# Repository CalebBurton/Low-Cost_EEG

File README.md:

# Low-Cost EEG
___Repo for storing files related to the Low-Cost EEG project at Stellenbosch University during the 2018 Global Health Technologies exchange with Northwestern University.___

---

Hardware is modified from the [OpenBCI Ganglion](https://github.com/OpenBCI/Ganglion_Hardware_Design_Files), firmware is copied directly from the [Ganglion library](https://github.com/OpenBCI/OpenBCI_Ganglion_Library) with no modification.

All design files were made with [KiCad](http://kicad-pcb.org/) EDA software.

Tested with Arduino IDE v1.8.5, utilizing Simblee library v1.1.4 from [https://www.simblee.com/package_simblee166_index.json](https://www.simblee.com/package_simblee166_index.json). See [this page](https://www.simblee.com/support.html) for instructions on adding an external board to your board manager.

Programmed using an [FTDI cable](https://www.adafruit.com/product/70). FTDI drivers are not yet supported on macOS versions 10.11.0 and above, so programming was done in a Windows 10 virtual machine.

The OpenBCI GUI, used for visualizing and analyzing the output data, can be downloaded from [OpenBCI's downloads page](http://openbci.com/index.php/downloads). OpenBCI also provides documentation for the [Ganglion](http://docs.openbci.com/Tutorials/02-Ganglion_Getting%20Started_Guide) and the [GUI](http://docs.openbci.com/OpenBCI%20Software/01-OpenBCI_GUI).

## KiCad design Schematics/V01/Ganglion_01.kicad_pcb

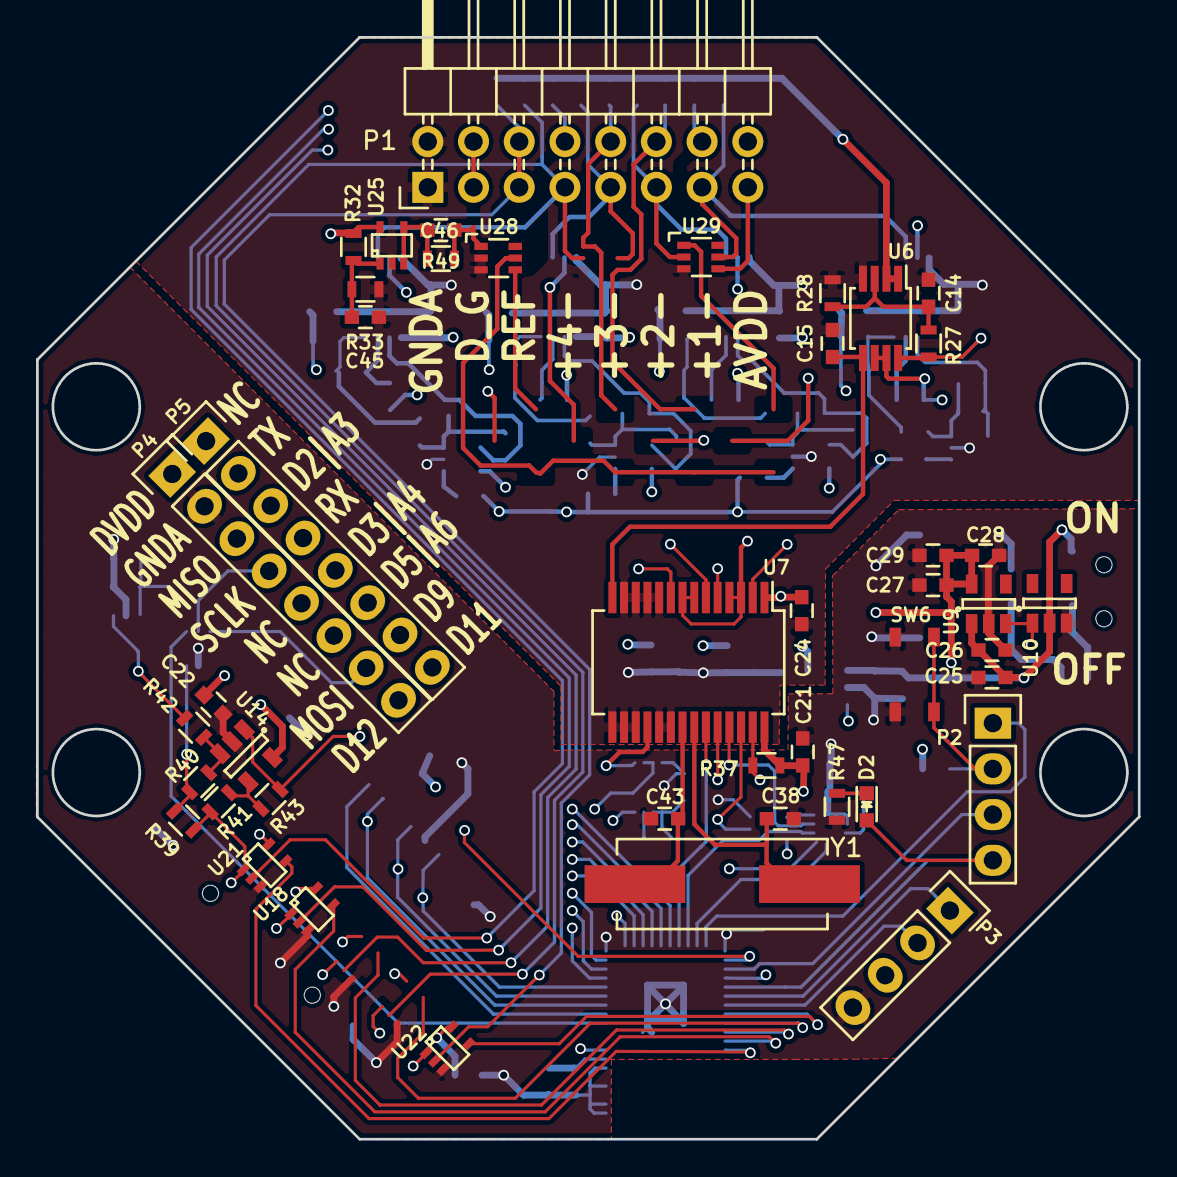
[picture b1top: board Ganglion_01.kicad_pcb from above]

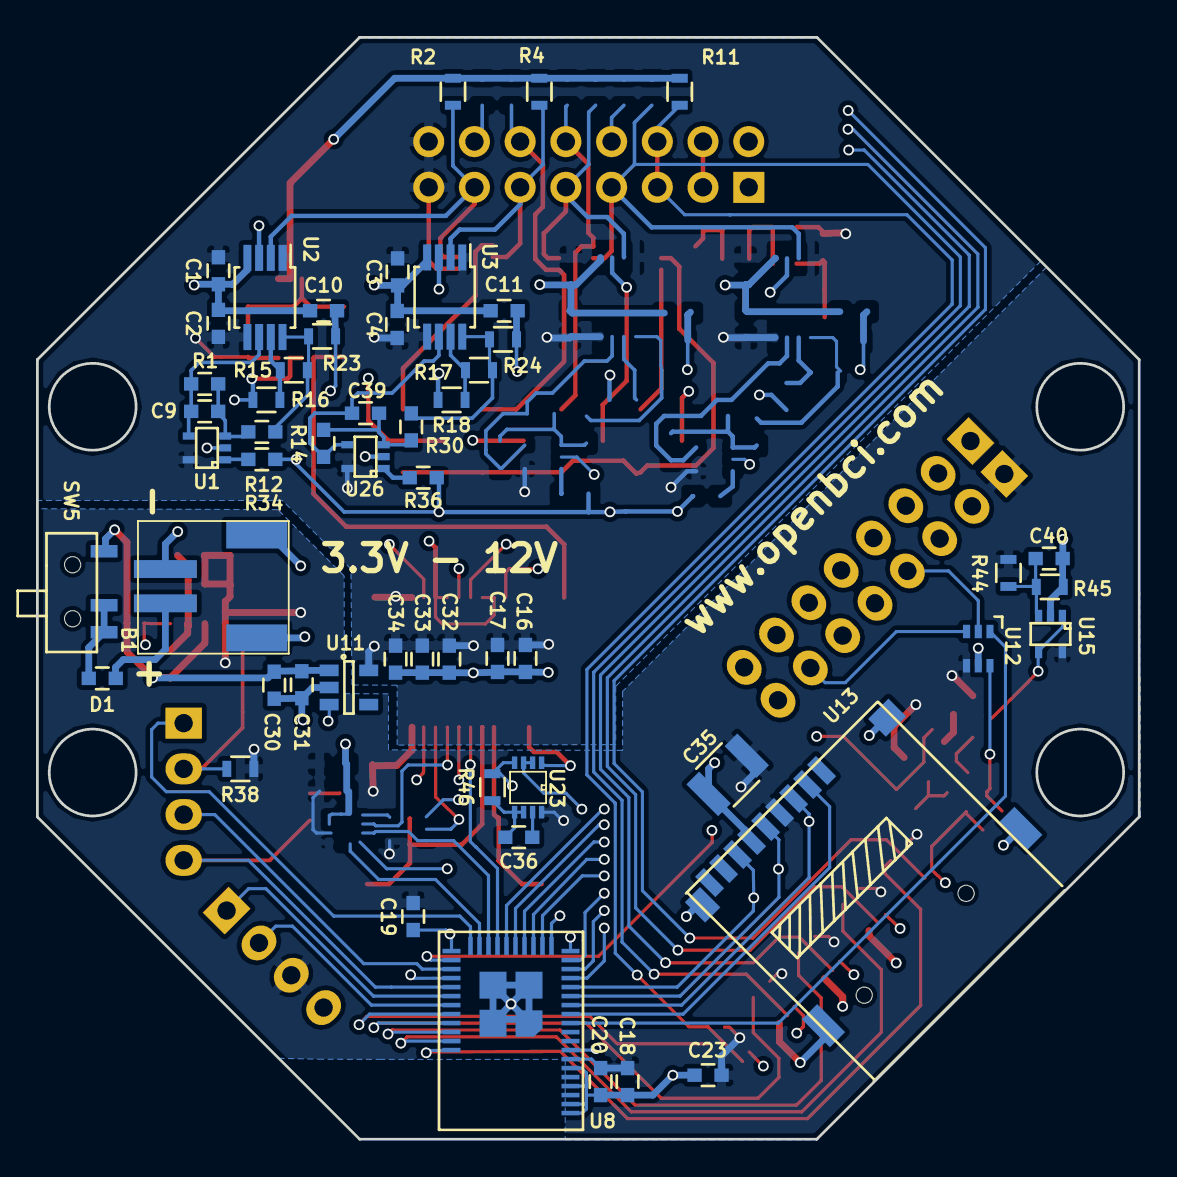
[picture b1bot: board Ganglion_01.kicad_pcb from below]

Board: 4 copper layers, 61.2 x 61.2 mm, 99 parts (54 on the bottom side), 67 nets.

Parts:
B1: JS_2_Battery; JST_RA_SMT
C1, C2, C3, C4, C15, C16, C20, C21, C22, C24, C26, C27, C31, C32: 0.1uF; C_0603
C9, C39: 22uF; C_0603
C10, C11, C14, C17, C19, C23, C25, C28, C30, C33, C40, C45, C46: 1uF; C_0603
C18, C29, C34: 10uF; C_0603
C35: 100uF; C_1210
C36: 0.01uF; C_0603
C38, C43: 18pF; C_0603
D1: D_Schottky; C_0603
D2: LED; LED_0603
P1: CONN_02X08; Pin_Header_Angled_2x08
P2, P3: CONN_01X04; Socket_Strip_Straight_1x04
P4, P5: CONN_01X08; Socket_Strip_Straight_1x08
R1, R12, R14, R30: 1M; C_0603
R2, R4, R11, R49: 330K; R_0603
R15, R17, R27, R28, R32, R33, R37, R44, R45, R46: 100K; R_0603
R16, R18: 2K; R_0603
R23, R24, R40, R41, R47: 1K; R_0603
R34, R36: 500K; C_0603
R38: 10K; R_0603
R39: 100; R_0603
R42, R43: 1M; R_0603
SW5: SPDT; SSSS810701SSSS810701
SW6: TACT_SWITCH; PTS810
U1, U25, U26: MCP6V31U; SC-70-5
U2, U3: AD8237; MSOP-8_3x3mm_Pitch0.65mm
U6: LM7332; MSOP-8_3x3mm_Pitch0.65mm
U7: MCP3912; SSOP-28_5.3x10.2mm_Pitch0.65mm
U8: rfd_77101; RFD77101
U9, U11: NCP551; SOT-23-5
U10: NCP300; SOT-23-5
U12: AD5621; SC-70-6
U13: SEEED_microSD; ST-TF-0003A
U14: MCP6V13T; SOT-23-5
U15: MCP6001; SC-70-5
U18, U21, U22: 74LVC1G66; SC-70-5
U23: 74LVC2G00; VSSOP-8
U28, U29: TPD4E1B06; SC-70-6
Y1: Crystal_Small; Crystal_HC49-SD_SMD

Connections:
1_IN+: P1.13, R2.1, U2.2, U21.2, U29.5
2_IN+: P1.11, R4.1, U3.2, U18.2, U29.2
/D_2|A_3: P5.3, U8.24
/D_3|A_4: P5.5, U8.22
/D_4|A_5: P2.3, U8.32
/D_5|A_6: P5.6, U8.21
/D_9: P5.7, U8.18
/D_11: P5.8, U8.17
/D_12: P4.8, U8.16
/D_14: P2.1, U8.29
/D_21: P3.2, U8.36
/D_23: D2.2, P2.4, U8.34
/D_24: P3.1, U8.35
/MCP_RST: R37.2, U7.27, U8.33
/MCP_SS: U7.23, U8.26
/REF+_OUT: C15.1, U6.5, U7.14
/SENSORS/IMP_SIG: R39.2, R41.2, U18.1, U21.1, U22.1
/SIM_RST: P2.2, R38.1, SW6.3, SW6.4, U8.8
/SIM_RX: P5.4, U8.23
/SIM_TX: P5.2, U8.25
/V_BATT: D1.1, SW5.2, SW5.3
/V_ENABLE: U9.3, U10.1, U11.3
/V_IN: C25.2, C26.2, C30.2, C31.2, SW5.1, U9.1, U10.2, U11.1
DAC_SS: U8.11, U12.1
DRDY: U8.20, U23.2, U23.3
D_G: C46.2, P1.3, R49.2, U28.1
GNDA: B1.2, B1.3, B1.4, C1.2, C2.2, C3.2, C4.2, C10.1, C11.2, C14.2, C15.2, C16.2, C17.2, C18.2, C19.2, C20.2, C21.1, C22.2, C23.2, C24.1, C25.1, C26.1, C27.1, C28.1, C29.1, C30.1, C31.1, C32.1, C33.1, C34.1, C35.1, C38.1, C40.2, C43.1, C45.2, P1.1, P3.4, P4.2, R28.2, R33.2, R45.2, R46.2, R47.2, SW6.1, SW6.2, U1.2, U2.4, U3.4, U6.4, U7.10, U7.11, U7.12, U7.13, U7.15, U7.16, U7.17, U7.19, U7.20, U8.1, U8.2, U8.4, U8.6, U8.19, U8.30, U8.42, U8.43, U8.44, U8.45, U9.2, U10.3, U11.2, U12.5, U13.6, U13.10, U13.11, U13.12, U13.13, U14.2, U15.2, U18.3, U21.3, U22.3, U23.4, U25.2, U26.2, U28.2, U28.3, U29.3
I_BIAS: R2.2, R4.2, R11.1, U6.1, U6.2
MCP_DRDY: U7.18, U23.1
MISO: P4.3, U7.25, U8.15, U13.7
MOSI: P4.7, U7.26, U8.13, U12.3, U13.3
unnamed: B1.1, D1.2
unnamed: C9.1, R1.1, R12.2, U1.3
unnamed: C10.2, R23.1, U7.2
unnamed: C11.1, R24.1, U7.5
unnamed: C14.1, R27.2, R28.1, U6.3
unnamed: C36.1, U23.7
unnamed: C36.2, R46.1, U23.5, U23.6
unnamed: C38.2, U7.22, Y1.1
unnamed: C39.1, R14.1, R30.2, U26.3
unnamed: C40.1, R44.2, R45.1, U15.3
unnamed: C43.2, U7.21, Y1.2
unnamed: C45.1, R32.2, R33.1, U25.1
unnamed: C46.1, R49.1, U25.3, U25.4
unnamed: D2.1, R47.1
unnamed: R15.1, R16.1, U2.7
unnamed: R17.1, R18.1, U3.7
unnamed: R34.2, U1.1
unnamed: R36.2, U26.1
unnamed: R39.1, R40.2, U12.6
unnamed: R40.1, R42.2, U14.3
unnamed: R41.1, R43.2, U14.4
unnamed: R42.1, U15.1, U15.4
OUT_1: R12.1, R15.2, R23.2, U2.8
OUT_2: R17.2, R24.2, R30.1, U3.8
REF: P1.5, R11.2, U2.3, U3.3, U22.2, U28.5
REF_1: C9.2, R1.2, U1.4, U2.6
REF_2: C39.2, R14.2, U3.6, U26.4
SCK: P4.4, U7.24, U8.14, U12.2, U13.5
SD_SS: U8.12, U13.2
VAA: C1.1, C2.1, C3.1, C4.1, C16.1, C17.1, C24.2, C32.2, C33.2, C34.2, P1.15, R27.1, R32.1, U1.5, U2.1, U2.5, U3.1, U3.5, U6.8, U7.1, U11.5, U25.5, U26.5, U29.4
VDD: C18.1, C19.1, C20.1, C21.2, C22.1, C23.1, C27.2, C28.2, C29.2, C35.2, P3.3, P4.1, R37.1, R38.2, R44.1, U7.28, U8.7, U9.5, U12.4, U13.4, U14.5, U15.5, U18.5, U21.5, U22.5, U23.8
V_REF: R16.2, R18.2, R34.1, R36.1, U6.6, U6.7, U7.3, U7.4, U7.7, U7.8
Z_TEST_1: U8.41, U21.4
Z_TEST_2: U8.40, U18.4
Z_TEST_REF: U8.37, U22.4
uA_SENS: R43.1, U8.31, U14.1

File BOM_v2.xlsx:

Item | Reference | Value | Footprint | Description | Digikey Part No. | Link to Digikey Page | Qty | Cost (Each) | Cost (Total)
1 | C38, C43 | 18pF | Through Hole | Capacitor 18pF | (Generic component) | (Generic component) | 2 |  | 0
2 | C36 | 0.01uF | Through Hole | Capacitor 0.01uF | (Generic component) | (Generic component) | 1 | 0 | 0
3 | C1, C2, C3, C4, C15, C16, C20, C21, C22, C24, C26, C27, C31, C32 | 0.1uF | Through Hole | Capacitor 0.1uF | (Generic component) | (Generic component) | 14 | 0 | 0
4 | C10, C11, C14, C17, C19, C23, C25, C28, C30, C33, C40, C45, C46 | 1uF | Through Hole | Capacitor 1uF | (Generic component) | (Generic component) | 13 | 0 | 0
5 | C18, C29, C34 | 10uF | Through Hole | Capacitor 10uF | (Generic component) | (Generic component) | 3 | 0 | 0
6 | C9, C39 | 22uF | Through Hole | Capacitor 22uF | (Generic component) | (Generic component) | 2 | 0 | 0
7 | C35 | 47uF | Through Hole | Capacitor 47uF | (Generic component) | (Generic component) | 1 | 0 | 0
8 | R39 | 100Ω | Through Hole | Resistor 100 | (Generic component) | (Generic component) | 1 | 0 | 0
9 | R23, R24, R40, R41, R47 | 1K | Through Hole | Resistor 1k | (Generic component) | (Generic component) | 5 | 0 | 0
10 | R16, R18 | 2K | Through Hole | Resistor 2k | (Generic component) | (Generic component) | 2 | 0 | 0
11 | R38 | 10K | Through Hole | Resistor 10k | (Generic component) | (Generic component) | 1 | 0 | 0
12 | R15, R17, R27, R28, R32, R33, R37, R44, R45, R46 | 100K | Through Hole | Resistor 100k | (Generic component) | (Generic component) | 10 | 0 | 0
13 | R2, R4, R11, R49 | 330K | Through Hole | Resistor 330k | (Generic component) | (Generic component) | 4 | 0 | 0
14 | R34, R36 | 500K | Through Hole | Resistor 500k | (Generic component) | (Generic component) | 2 | 0 | 0
15 | R1, R12, R14, R30, R42, R43 | 1M | Through Hole | Resistor 1M | (Generic component) | (Generic component) | 6 | 0 | 0
16 | BT1 | - | 1053 | LIR2450 Battery Holder | 36-1053-ND | 36-1053-ND | 1 | 2 | 2
17 | D1 | - | Through Hole | Schottky diode | 497-2492-1-ND | https://www.digikey.com/product-detail/en/stmicroelectronics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 | 1 | 0.47 | 0.47
18 | D2 | BLUE | Through Hole | Power indicator LED | 754-1914-ND | https://www.digikey.com/product-detail/en/kingbright/WP710A1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 | 1 | 0.56000000000000005 | 0.56000000000000005
19 | SW5 | SPDT | 3-pin SIP | Toggle switch | EG1903-ND | https://www.digikey.com/product-detail/en/e-switch/EG1218/EG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 | 1 | 0.57999999999999996 | 0.57999999999999996
20 | SW6 | SPST (NO) | Through Hole | Tactile switch (reset button) | P8082SCT-ND | https://www.digikey.com/product-detail/en/panasonic-electron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 | 1 | 0.23 | 0.23
21 | U1, U25, U26 | - | 8-pin DIP | Op Amp | TC7650CPA-ND | https://www.digikey.com/product-detail/en/microchip-technolo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 | 3 | 3.61 | 10.83
22 | U2, U3 | - | 8-pin DIP | Instrumentation Amp | AD627ANZ-ND | https://www.digikey.com/product-detail/en/analog-devices-inc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 | 2 | 8.5299999999999994 | 17.059999999999999
23 | U6 | - | 8-pin DIP | Op Amp | 296-34316-5-ND | https://www.digikey.com/product-detail/en/texas-instruments/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 | 1 | 0.84 | 0.84
24 | U7 | - | 28-pin SSOP | 4-channel ADC | MCP3912A1-E/SS-ND | https://www.digikey.com/product-detail/en/microchip-technolo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 | 1 | 3.42 | 3.42
25 | U7 | - | 28-pin DIP breakout | SSOP Breakout board | PA0020-ND | https://www.digikey.com/product-detail/en/chip-quik-inc/PA00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 | 1 | 5.79 | 5.79
26 | U8 | - | 34-pin (16/18) DIP breakout | Simblee BLE/MCU dev board | 1568-1353-ND | https://www.digikey.com/product-detail/en/sparkfun-electroni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 | 1 | 24.95 | 24.95
27 | U9, U11 | 3V | 8-pin DIP | Llinear voltage regulators | 296-1965-5-ND | https://www.digikey.com/product-detail/en/texas-instruments/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 | 2 | 2.0099999999999998 | 4.0199999999999996
28 | U12 | - | 8-pin DIP | 12-bit DAC (for Z test) | MCP4921-E/P-ND | https://www.digikey.com/product-detail/en/microchip-technolo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 | 1 | 2.09 | 2.09
29 | U13 | - | 7-pin SIP breakout | Micro SD card holder | 1568-1345-ND | https://www.digikey.com/product-detail/en/sparkfun-electroni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 | 1 | 3.95 | 3.95
30 | U10 | - | 8-pin DIP | Voltage detector (for clean reset) | 296-11547-5-ND | https://www.digikey.com/product-detail/en/texas-instruments/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 | 1 | 3.76 | 3.76
31 | U14 | - | 8-pin DIP | Op Amp | LTC1152CN8#PBF-ND | https://www.digikey.com/product-detail/en/linear-technology-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 | 1 | 6.15 | 6.15
32 | U15 | - | 8-pin DIP | Op Amp | MCP6002-I/P-ND | https://www.digikey.com/product-detail/en/microchip-technolo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 | 1 | 0.35 | 0.35
33 | U18, U21, U22 | - | 8-pin DIP | Electric switches (for Z tests) | 296-21908-5-ND | https://www.digikey.com/product-detail/en/texas-instruments/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 | 3 | 0.76 | 2.2800000000000002
34 | U23 | - | 8-pin DIP | 2-input NAND gates (2 per package) | 296-3504-5-ND | https://www.digikey.com/product-detail/en/texas-instruments/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 | 1 | 0.54 | 0.54
35 | U28, U29 | - | Through Hole | 6V Zener diodes (input protection) | 1N5234BFSCT-ND | https://www.digikey.com/product-detail/en/on-semiconductor/1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 | 8 | 0.121 | 0.96799999999999997
36 | Y1 | 3.2768 MHz | HC49/U | Crystal oscillator | X980-ND | https://www.digikey.com/product-detail/en/ecs-inc/ECS-32-17-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 | 1 | 0.6 | 0.6
 |  |  |  |  |  |  |  |  | 91.438000000000017

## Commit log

2018-03-19 Porting from fork of Ganglion repo
2018-03-19 Adding gitignore
2018-03-20 Update BOM
2018-03-20 Update BOM to match new schematic refs
2018-03-20 Remove datasheets folder, use the links in the BoM
2018-03-20 Update ESD protection block
2018-03-20 Fixed typo in BOM
2018-03-20 Added demo video
2018-03-20 Update instrumentation amps with DIP replacements
2018-03-20 Remove two unnecessary bypass capacitors
